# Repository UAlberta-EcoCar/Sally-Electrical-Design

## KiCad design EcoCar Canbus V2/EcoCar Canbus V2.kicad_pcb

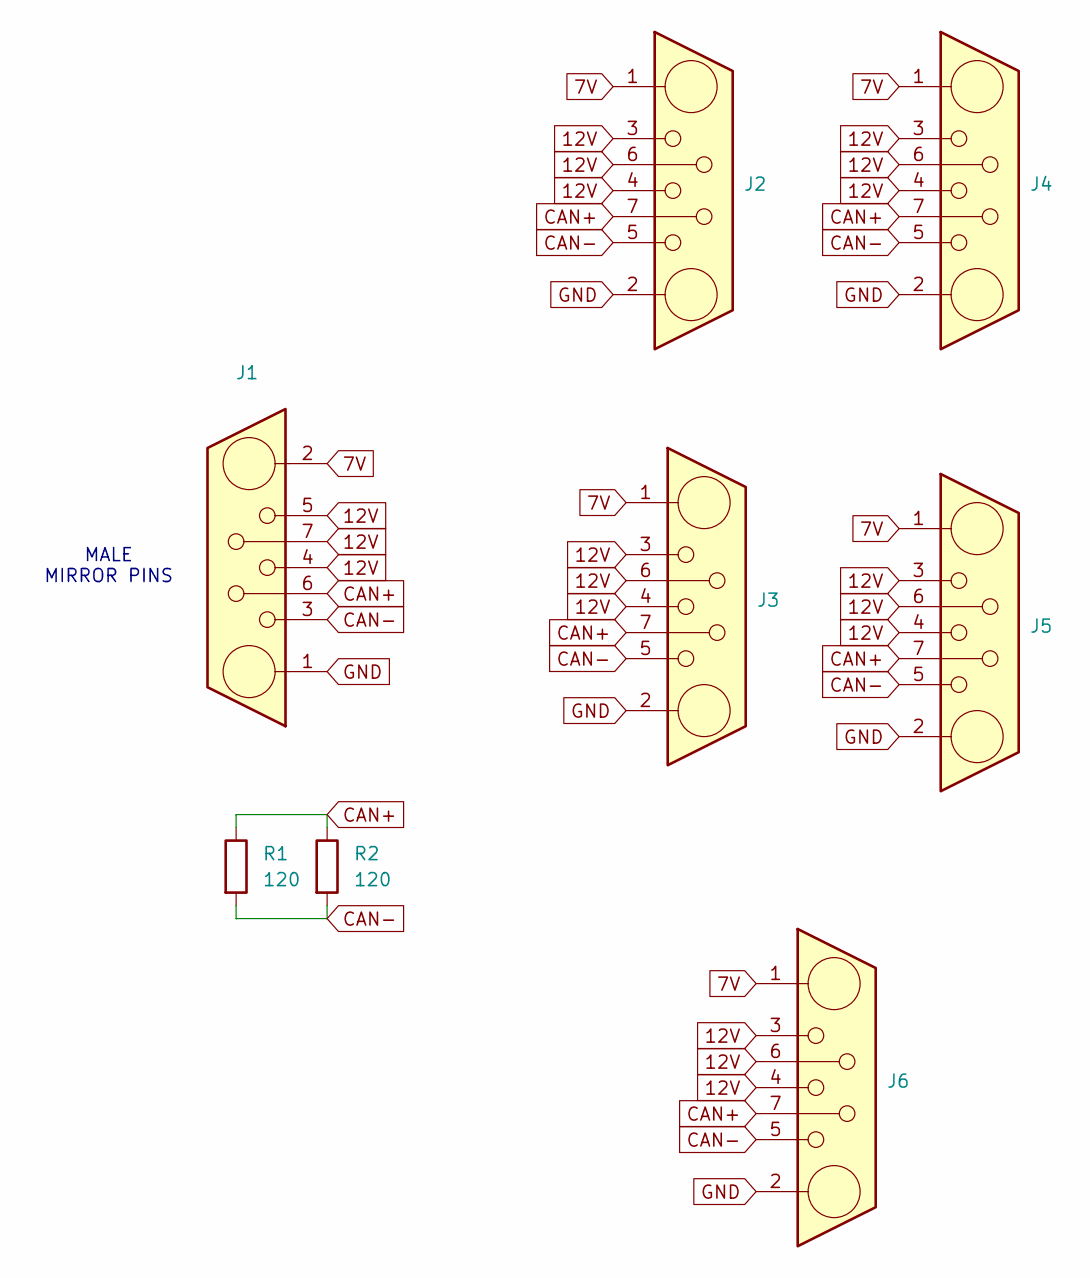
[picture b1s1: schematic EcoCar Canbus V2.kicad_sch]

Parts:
J1, J2, J3, J4, J5, J6: DB7W2-30A
R1, R2: 120; R_Axial_DIN0207_L6.3mm_D2.5mm_P7.62mm_Horizontal

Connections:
7V: J1.2, J2.1, J3.1, J4.1, J5.1, J6.1
12V: J1.4, J1.5, J1.7, J2.3, J2.4, J2.6, J3.3, J3.4, J3.6, J4.3, J4.4, J4.6, J5.3, J5.4, J5.6, J6.3, J6.4, J6.6
CAN+: J1.6, J2.7, J3.7, J4.7, J5.7, J6.7, R1.1, R2.1
CAN-: J1.3, J2.5, J3.5, J4.5, J5.5, J6.5, R1.2, R2.2
GND: J1.1, J2.2, J3.2, J4.2, J5.2, J6.2

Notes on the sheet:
MALE MIRROR PINS

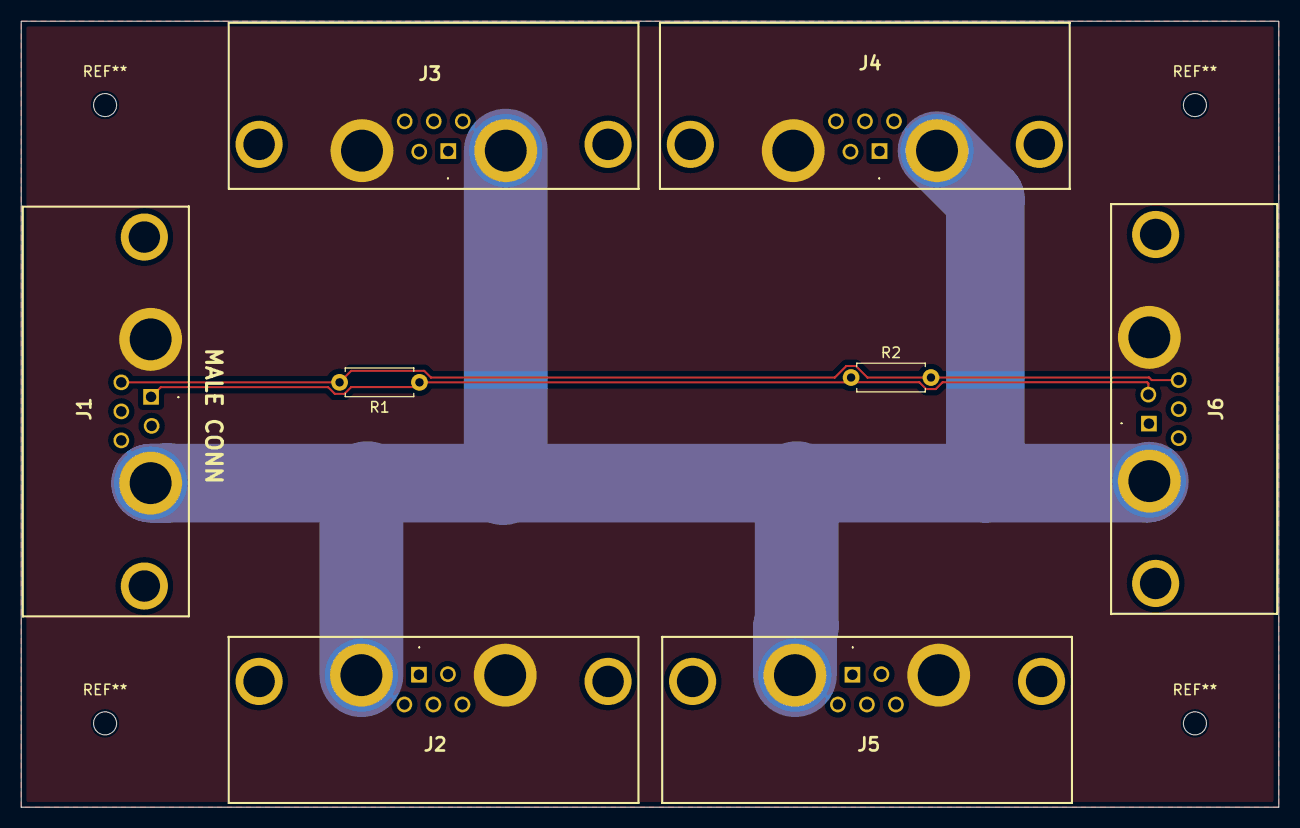
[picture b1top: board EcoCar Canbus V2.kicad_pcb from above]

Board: 4 copper layers, 120.0 x 75.0 mm, 8 parts (0 on the bottom side), 5 nets.

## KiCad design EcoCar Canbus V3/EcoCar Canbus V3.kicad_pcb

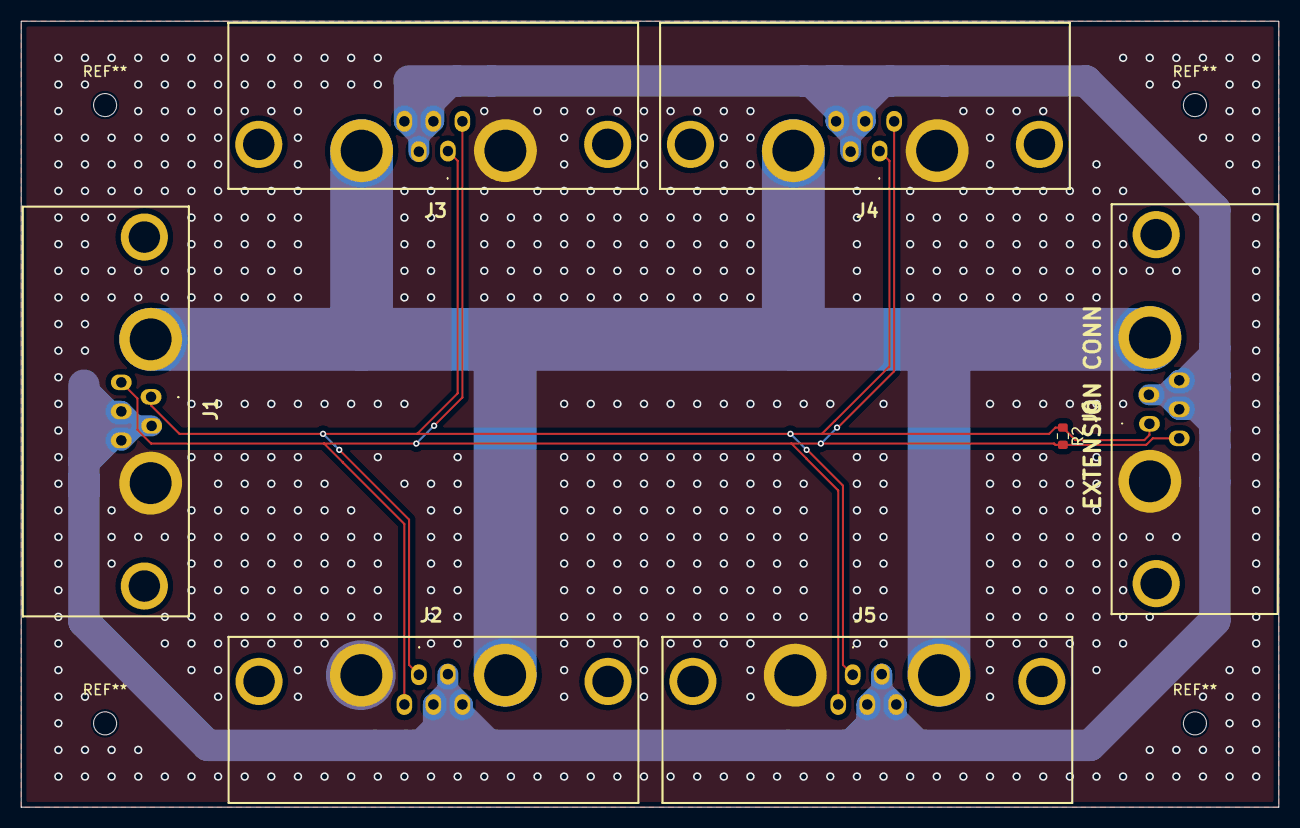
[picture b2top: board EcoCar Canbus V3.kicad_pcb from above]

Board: 4 copper layers, 120.0 x 75.0 mm, 7 parts (0 on the bottom side), 5 nets.

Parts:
J1: DB7W2-Male
J2, J3, J4, J5, J6: DB7W2-Female
R2: 120; R_0603_1608Metric

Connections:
7V: J1.A1, J2.8 (A1), J3.8 (A1), J4.8 (A1), J5.8 (A1), J6.8 (A1)
12V: J1.2, J1.4, J1.5, J2.1, J2.3, J2.4, J3.1, J3.3, J3.4, J4.1, J4.3, J4.4, J5.1, J5.3, J5.4, J6.1, J6.3, J6.4
CAN+: J1.1, J2.2, J3.2, J4.2, J5.2, J6.2, R2.1
CAN-: J1.3, J2.5, J3.5, J4.5, J5.5, J6.5, R2.2
GND: J1.A2, J2.9 (A2), J3.9 (A2), J4.9 (A2), J5.9 (A2), J6.9 (A2)

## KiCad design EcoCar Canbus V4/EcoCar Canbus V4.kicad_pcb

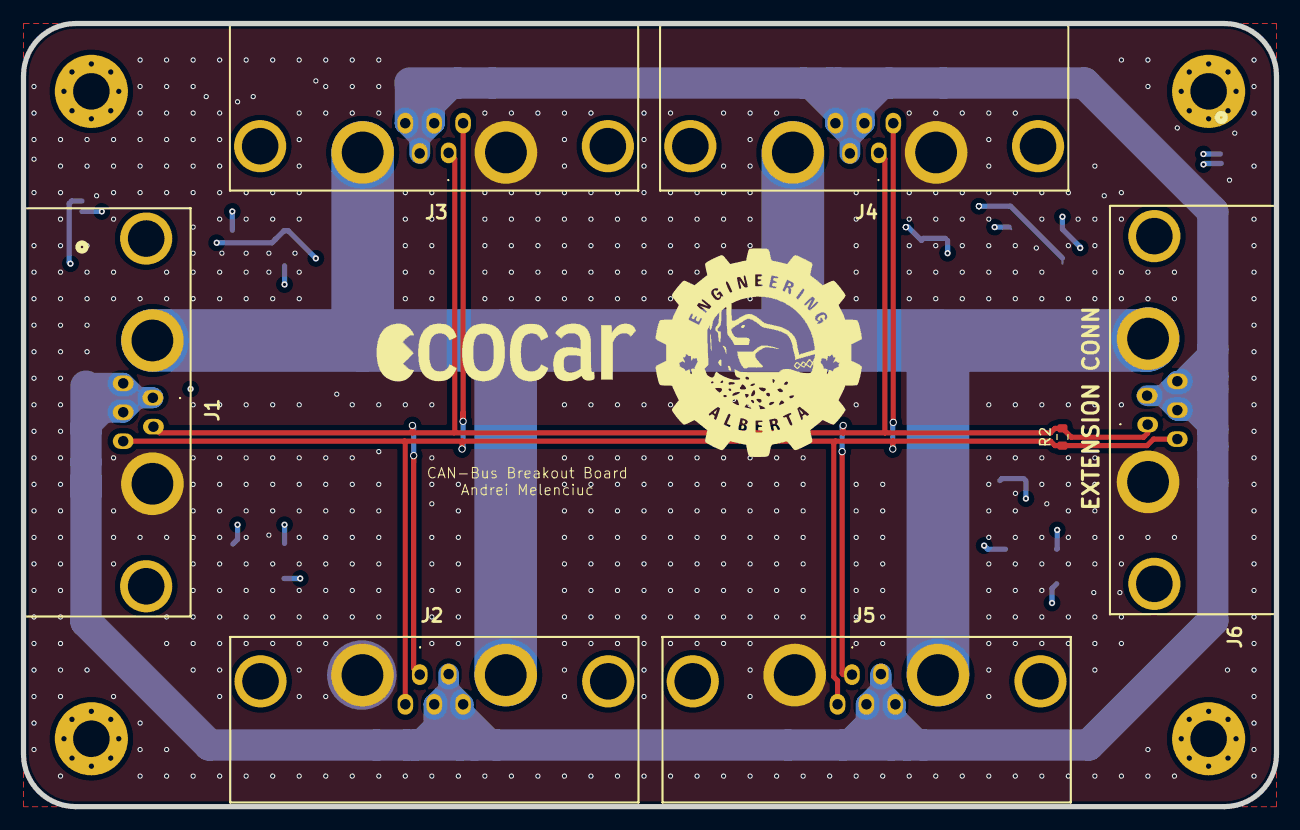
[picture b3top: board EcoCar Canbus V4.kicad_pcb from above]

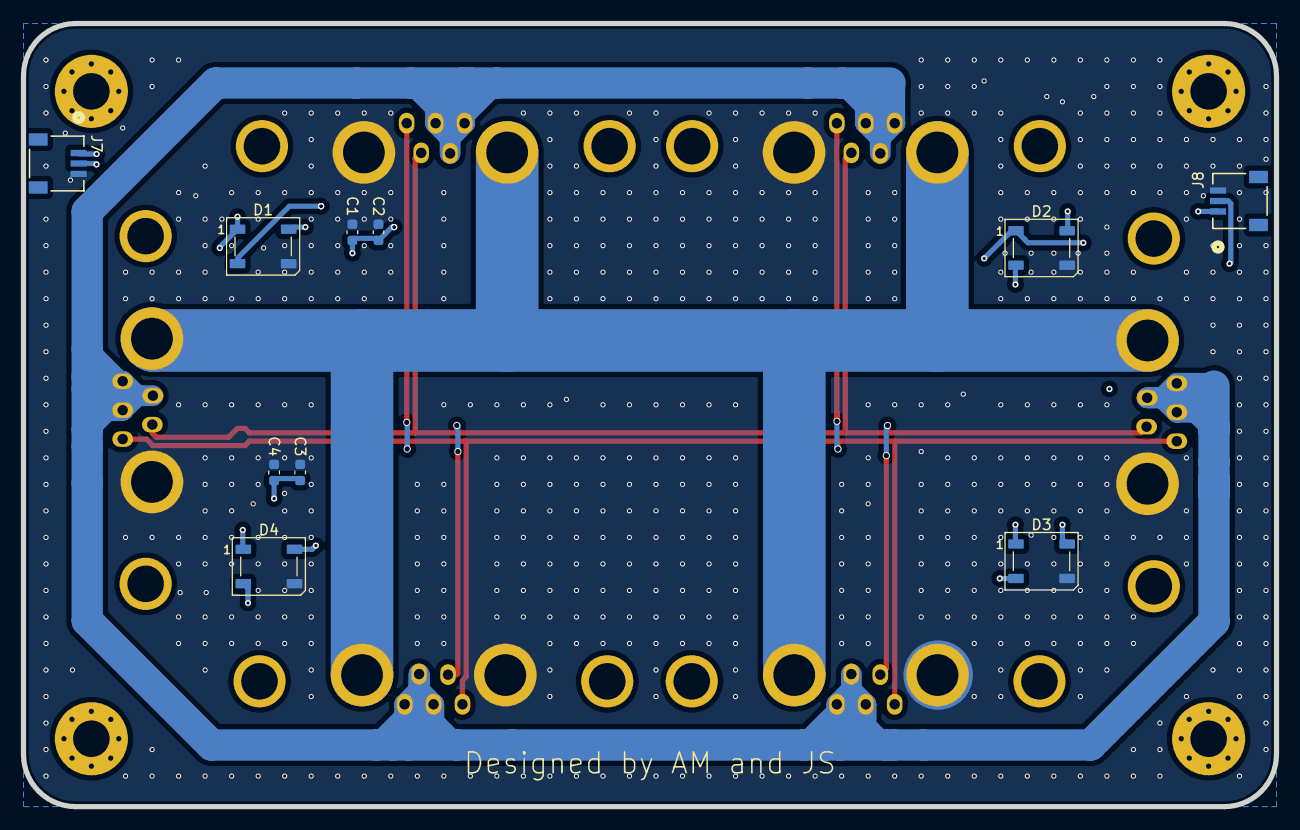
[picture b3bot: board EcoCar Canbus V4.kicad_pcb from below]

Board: 4 copper layers, 120.0 x 75.0 mm, 17 parts (10 on the bottom side), 11 nets.

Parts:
C1, C2, C3, C4: 1n; C_0603_1608Metric
D1, D2, D3, D4: WS2812B; LED_WS2812B_PLCC4_5.0x5.0mm_P3.2mm
J1: DB7W2-Male
J2, J3, J4, J5, J6: DB7W2-Female
J7, J8: Conn_01x03_Pin; CONN_SM03B-SRSS-TB_JST
R2: 120; R_0603_1608Metric

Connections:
7V: J1.8, J2.8, J3.8, J4.8, J5.8, J6.8
12V: J1.1, J1.3, J1.4, J2.1, J2.3, J2.4, J3.1, J3.3, J3.4, J4.1, J4.3, J4.4, J5.1, J5.3, J5.4, J6.1, J6.3, J6.4
+5V: C1.1, C2.1, C3.1, C4.1, D1.1 (VDD), D2.1 (VDD), D3.1 (VDD), D4.1 (VDD), J7.1, J8.1
/DIN: D1.4 (DIN), J7.2
/DOUT: D4.2 (DOUT), J8.2
CAN+: J1.2, J2.2, J3.2, J4.2, J5.2, J6.2, R2.1
CAN-: J1.5, J2.5, J3.5, J4.5, J5.5, J6.5, R2.2
GND: C1.2, C2.2, C3.2, C4.2, D1.3 (VSS), D2.3 (VSS), D3.3 (VSS), D4.3 (VSS), J1.9, J2.9, J3.9, J4.9, J5.9, J6.9, J7.3, J8.3
unnamed: D1.2 (DOUT), D2.4 (DIN)
unnamed: D2.2 (DOUT), D3.4 (DIN)
unnamed: D3.2 (DOUT), D4.4 (DIN)

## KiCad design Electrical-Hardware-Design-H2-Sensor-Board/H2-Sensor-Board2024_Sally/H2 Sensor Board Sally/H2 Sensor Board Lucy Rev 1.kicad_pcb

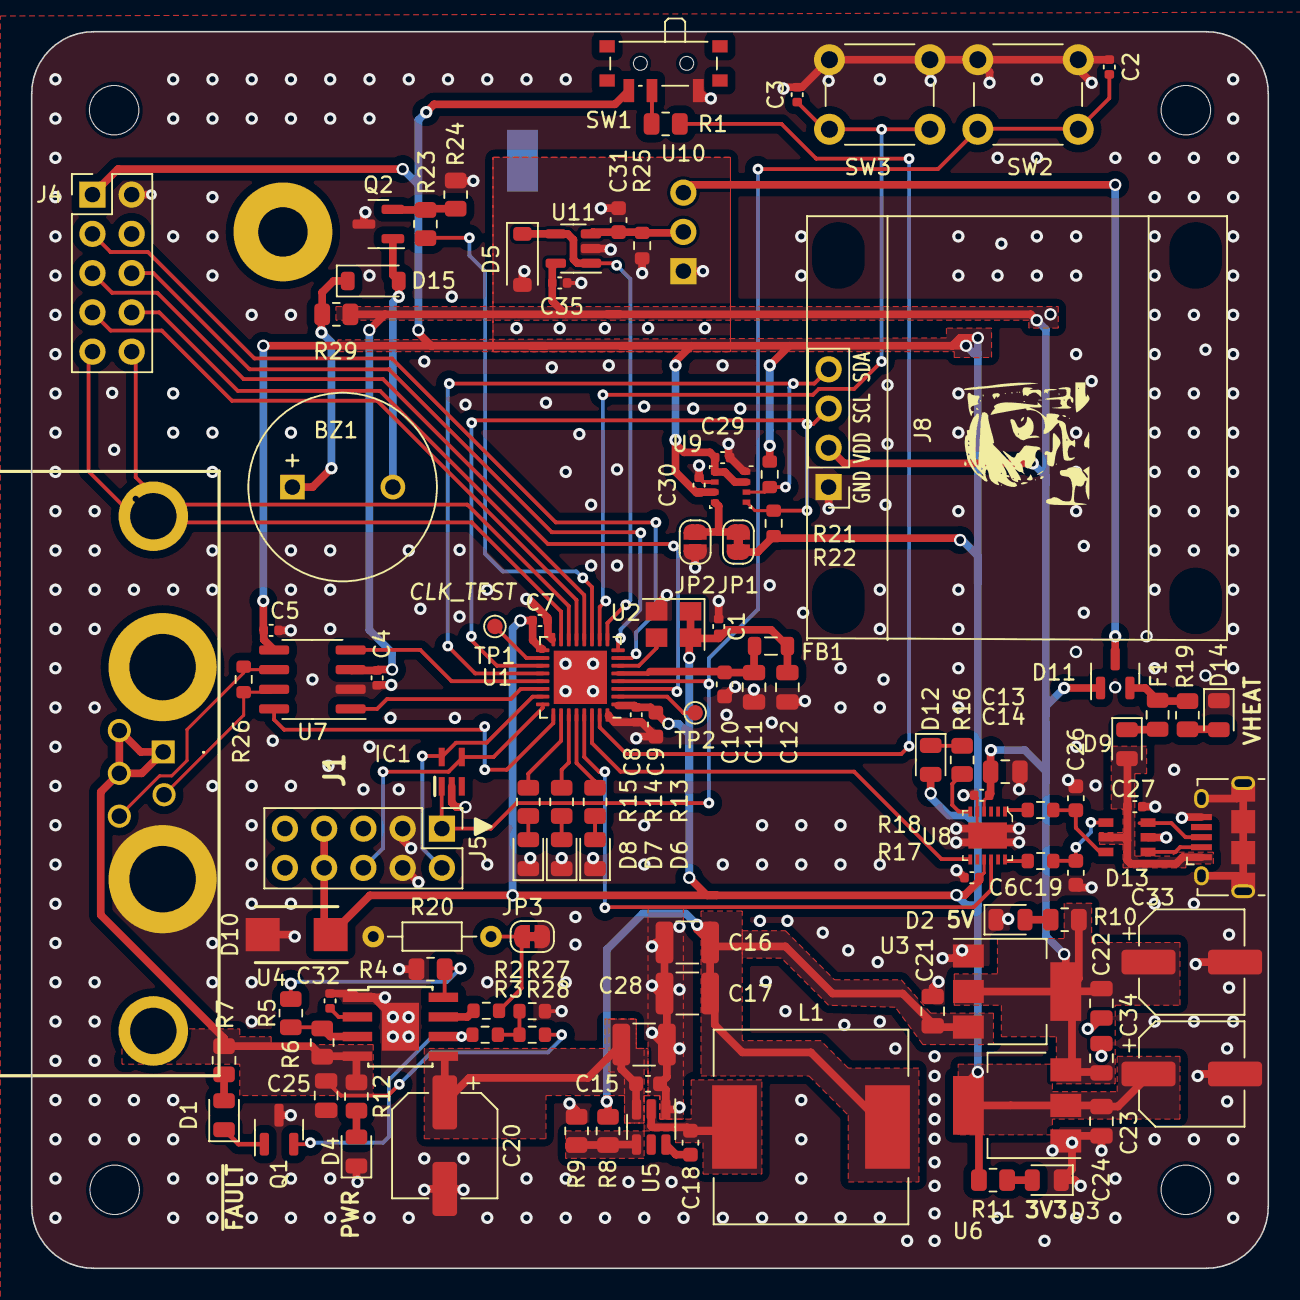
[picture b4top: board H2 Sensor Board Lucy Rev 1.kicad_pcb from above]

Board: 2 copper layers, 80.0 x 80.0 mm, 115 parts (1 on the bottom side), 74 nets.

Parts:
BZ1: Buzzer; MagneticBuzzer_ProSignal_ABT-410-RC
C1, C2, C3, C4, C5, C6, C7, C8, C14, C27, C29, C30, C35: 100n; C_0402_1005Metric
C9, C10: 10u; C_0603_1608Metric
C11, C12: 1u; C_0805_2012Metric
C13: 4u7; C_0805_2012Metric
C15, C18, C31: 100n; C_0603_1608Metric
C16, C17: 22u; C_1210_3225Metric
C19, C26: 47p; C_0603_1608Metric
C20: 100u; CP_Elec_6.3x5.9
C21, C23: 10u; C_0805_2012Metric
C22, C24: 22u; C_0805_2012Metric
C25: 100n; C_0805_2012Metric
C28: 10u; C_1210_3225Metric
C32: 2n2; C_0402_1005Metric
C33, C34: 22u; CP_Elec_6.3x5.9
D1, D6: GREEN; LED_0805_2012Metric
D2, D3, D4, D14: BLUE; LED_0805_2012Metric
D5: MMSZ5226B-7-F; D_SOD-123
D7: RED; LED_0805_2012Metric
D8, D12: AMBER; LED_0805_2012Metric
D9: D_Schottky; D_0805_2012Metric
D10: SMLVT3V3; DIOM5436X265N
D11: BAT54C; SOT-23
D13: USBLC6-2SC6; SOT23-6L_STM
D15: BAV16W/1N4148W; D_SOD-123
F1: 500mA; Fuse_0805_2012Metric
FB1: 300R; L_0805_2012Metric
H1, H2, H3, H4: MountingHole; MountingHole_3.2mm_M3
IC1: ESDALC6V1W5; SOT65P210X110-5N
J1: DB7W2-30A
J4: GPIO; PinHeader_2x05_P2.54mm_Vertical
J5: Conn_02x05_Top_Bottom; PinHeader_2x05_P2.54mm_Vertical
J6: USB_B_Micro; USB_Micro-B_Amphenol_10118194_Horizontal
J8: OLED; Display_128x64_096_I2C
JP1: Slave Address LSB 1; SolderJumper-2_P1.3mm_Bridged_RoundedPad1.0x1.5mm
JP2: Slave Address LSB 0; SolderJumper-2_P1.3mm_Open_RoundedPad1.0x1.5mm
JP3: MAX CURRENT; SolderJumper-2_P1.3mm_Bridged_RoundedPad1.0x1.5mm
L1: 3u8; L_12x12mm_H8mm
NT1: NetTie_2; NetTie-2_SMD_Pad2.0mm
Q1: NMOS; SOT-23
Q2: NMOS IRLML2502TRPBF; SOT-23
R1, R24: 10k; R_0805_2012Metric
R2: 620R; R_0603_1608Metric
R3, R21, R22, R25: 4k7; R_0603_1608Metric
R4, R8: 47k; R_0805_2012Metric
R5: 23k7; R_0805_2012Metric
R6: 511k; R_0805_2012Metric
R7, R12: 2k; R_0805_2012Metric
R9: 6k2; R_0805_2012Metric
R10, R19: 560R; R_0805_2012Metric
R11, R13, R14, R15, R16: 220R; R_0805_2012Metric
R17, R18: 27R; R_0603_1608Metric
R20: R; R_Axial_DIN0204_L3.6mm_D1.6mm_P7.62mm_Horizontal
R23: 10R; R_0805_2012Metric
R26: 120R; R_0603_1608Metric
R27: 30k; R_0603_1608Metric
R28: 47k; R_0603_1608Metric
R29: 1k; R_0805_2012Metric
SW1: SW_SPDT; SW_SPDT_PCM12
SW2: RESET; SW_PUSH_6mm_H5mm
SW3: TARE; SW_PUSH_6mm_H5mm
TP1: MCO; TestPoint_Pad_D1.0mm
TP2: GPTP; TestPoint_Pad_D1.0mm
U1: STM32L432KCU6; QFN-32-1EP_5x5mm_P0.5mm_EP3.45x3.45mm
U2: 8MHz; Crystal_SMD_3225-4Pin_3.2x2.5mm
U3: AZ1117IH-5.0; SOT-223-3_TabPin2
U4: TPS2596; TI_SO-PowerPAD-8
U5: AP62250; TSOT-23-6
U6: AZ1117IH-3.3; SOT-223-3_TabPin2
U7: MCP2542FD-E/SN; SOIC-8_3.9x4.9mm_P1.27mm
U8: FT234XD-R; DFN-12-1EP_3x3mm
U9: BME280; Bosch_LGA-8_2.5x2.5mm_P0.65mm_ClockwisePinNumbering
U10: H2_Sensor_Daughter_Board_Rev_1
U11: AD8603; TSOT-23-5

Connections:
+3.3VA: C10.1, C11.1, FB1.1, U1.5 (VDDA)
+3V3: C1.2, C5.2, C6.1, C7.1, C8.1, C9.1, C12.1, C24.1, C29.1, C30.1, C34.1, D10.1 (K), D12.2 (A), FB1.2, J4.1, J5.7, J5.8, JP1.2 (B), R11.1, R21.1, R22.1, SW1.3 (C), U1.1 (VDD), U1.17 (VDD), U2.1 (~ST), U2.4 (VCC), U6.2 (VO), U7.5 (VIO), U8.9 (VCCIO), U9.2 (CSB), U9.6 (VDDIO), U9.8 (VDD)
+5V: C4.2, C13.1, C14.1, C22.1, C23.1, C33.1, C35.1, D11.1, J8.2, R10.1, R29.1, U3.2 (VO), U6.3 (VI), U7.3 (VDD), U8.4 (VCC), U11.5 (V+)
+12V: C15.1, C20.1, C28.1, U4.5 (OUT), U5.3 (VIN)
/12volts_sys: C25.1, J1.3, J1.4, J1.6, R6.2, R7.1, R12.1, R28.1, U4.4 (IN)
/BEEPER: R23.2, U1.11 (PA5)
/BOOT0: R1.2, U1.31 (PH3)
/CAN_RX: U1.21 (PA11), U7.4 (RXD)
/CAN_STBY: U1.25 (PA15), U7.8 (STBY)
/CAN_TX: U1.22 (PA12), U7.1 (TXD)
/CD+: J1.7, R26.1, U7.7 (CANH)
/CD-: J1.5, R26.2, U7.6 (CANL)
/DEBUG_SWCLK: IC1.4 (I/03), J5.6, U1.24 (PA14)
/DEBUG_SWDIO: IC1.5 (I/04), J5.2, U1.23 (PA13)
/GPIO1: J4.8, U1.12 (PA6)
/GPIO2: J4.10, U1.14 (PB0)
/GPIO3: J4.5, U1.3 (PC15)
/GPIO4: J4.6, U1.8 (PA2)
/GPIO7: J4.9, U1.15 (PB1)
/GPIO8: J4.7, U1.13 (PA7)
/GPIO9: J4.3, U1.7 (PA1)
/GPLED1: R15.2, U1.26 (PB3)
/GPLED2: R14.2, U1.27 (PB4)
/GPLED3: R13.2, U1.28 (PB5)
/H2_SENSE: D5.1 (K), U1.9 (PA3), U11.1, U11.4 (-)
/NRST: C2.2, IC1.1 (I/01), J5.1, SW2.2, U1.4 (NRST)
/Power/7V: C16.1, C17.1, C21.1, L1.2, R8.1, U3.3 (VI)
/Power/FB: R8.2, R9.2, U5.4 (FB)
/Power/I_{MON}: R2.1, U4.7 (ILM)
/Power/SW: C18.1, L1.1, U5.2 (SW)
/Power/~FAULT: Q1.2 (G), R3.1, U4.6 (~FAULT)
/SCL: J8.3, R22.2, U1.19 (PA9), U9.4 (SCK)
/SDA: J8.4, R21.2, U1.20 (PA10), U9.3 (SDI)
/Sensors/ADDR: JP1.1 (A), JP2.1 (A), U9.5 (SDO)
/Sensors/V_SENSE: C31.1, R25.2, U10.2 (V_SENSE), U11.3 (+)
/TARE: C3.2, SW3.2, U1.10 (PA4)
/UART_RX: U1.30 (PB7), U8.7 (TXD)
/UART_TX: U1.29 (PB6), U8.10 (RXD)
/XCLK: U1.6 (PA0), U2.3 (OUT)
GND: C1.1, C2.1, C3.1, C4.1, C5.1, C6.2, C7.2, C8.2, C9.2, C10.2, C11.2, C12.2, C13.2, C14.2, C15.2, C16.2, C17.2, C19.1, C20.2, C21.2, C22.2, C23.2, C24.2, C25.2, C26.1, C27.1, C28.2, C29.2, C30.2, C32.2, C33.2, C34.2, D2.1 (K), D3.1 (K), D4.1 (K), D6.1 (K), D7.1 (K), D8.1 (K), D10.2 (A), D13.2, D14.1 (K), IC1.2 (GND), J1.2, J4.2, J5.3, J5.4, J6.5 (GND), J6.6 (Shield), J8.1, JP2.2 (B), JP3.2 (B), NT1.2, Q1.3 (S), Q2.3 (S), R4.2, R9.1, R20.1, R24.2, R27.1, SW1.1 (A), SW2.1, SW3.1, U1.16 (VSS), U1.32 (VSS), U1.33 (VSS), U2.2 (GND), U3.1 (GND), U4.1 (GND), U4.9 (PAD), U5.1 (GND), U6.1 (GND), U7.2 (VSS), U8.5 (GND), U8.13 (GND), U9.1 (GND), U9.7 (GND)
GNDA: C31.2, C35.2, D5.2 (A), NT1.1, R25.1, U10.1 (GND), U11.2 (V-)
unnamed: BZ1.2 (+), D15.2 (A), Q2.1 (D)
unnamed: BZ1.1 (-), D15.1 (K), R29.2
unnamed: C19.2, D13.4, R17.2
unnamed: C26.2, D13.6, R18.2
unnamed: D1.2 (A), R7.2
unnamed: D1.1 (K), Q1.1 (D)
unnamed: D2.2 (A), R10.2
unnamed: D3.2 (A), R11.2
unnamed: D4.2 (A), R12.2
unnamed: D6.2 (A), R13.1
unnamed: D7.2 (A), R14.1
unnamed: D8.2 (A), R15.1
unnamed: D9.1 (K), F1.1
unnamed: D12.1 (K), R16.2
unnamed: D14.2 (A), R19.2
unnamed: D13.3, J6.3 (D+)
unnamed: D13.1, J6.2 (D-)
unnamed: JP3.1 (A), R2.2, R20.2
unnamed: Q2.2 (G), R23.1, R24.1
unnamed: R3.2, R27.2, R28.2
unnamed: R1.1, SW1.2 (B)
unnamed: TP1.1, U1.18 (PA8)
unnamed: TP2.1, U1.2 (PC14)
unnamed: R5.1, R6.1, U4.3 (EN/UVLO)
unnamed: R4.1, R5.2, U4.8 (OVLO)
unnamed: C32.1, U4.2 (dV/dT)
unnamed: C18.2, U5.6 (BST)
unnamed: R16.1, U8.6 (CBUS0)
unnamed: R18.1, U8.1 (USBDM)
unnamed: R17.1, U8.12 (USBDP)
unnamed: D11.3, U10.3 (V_HEAT)
VBUS_UP: C27.2, D9.2 (A), D13.5, J6.1 (VBUS)
V_HEAT: D11.2, F1.2, R19.1

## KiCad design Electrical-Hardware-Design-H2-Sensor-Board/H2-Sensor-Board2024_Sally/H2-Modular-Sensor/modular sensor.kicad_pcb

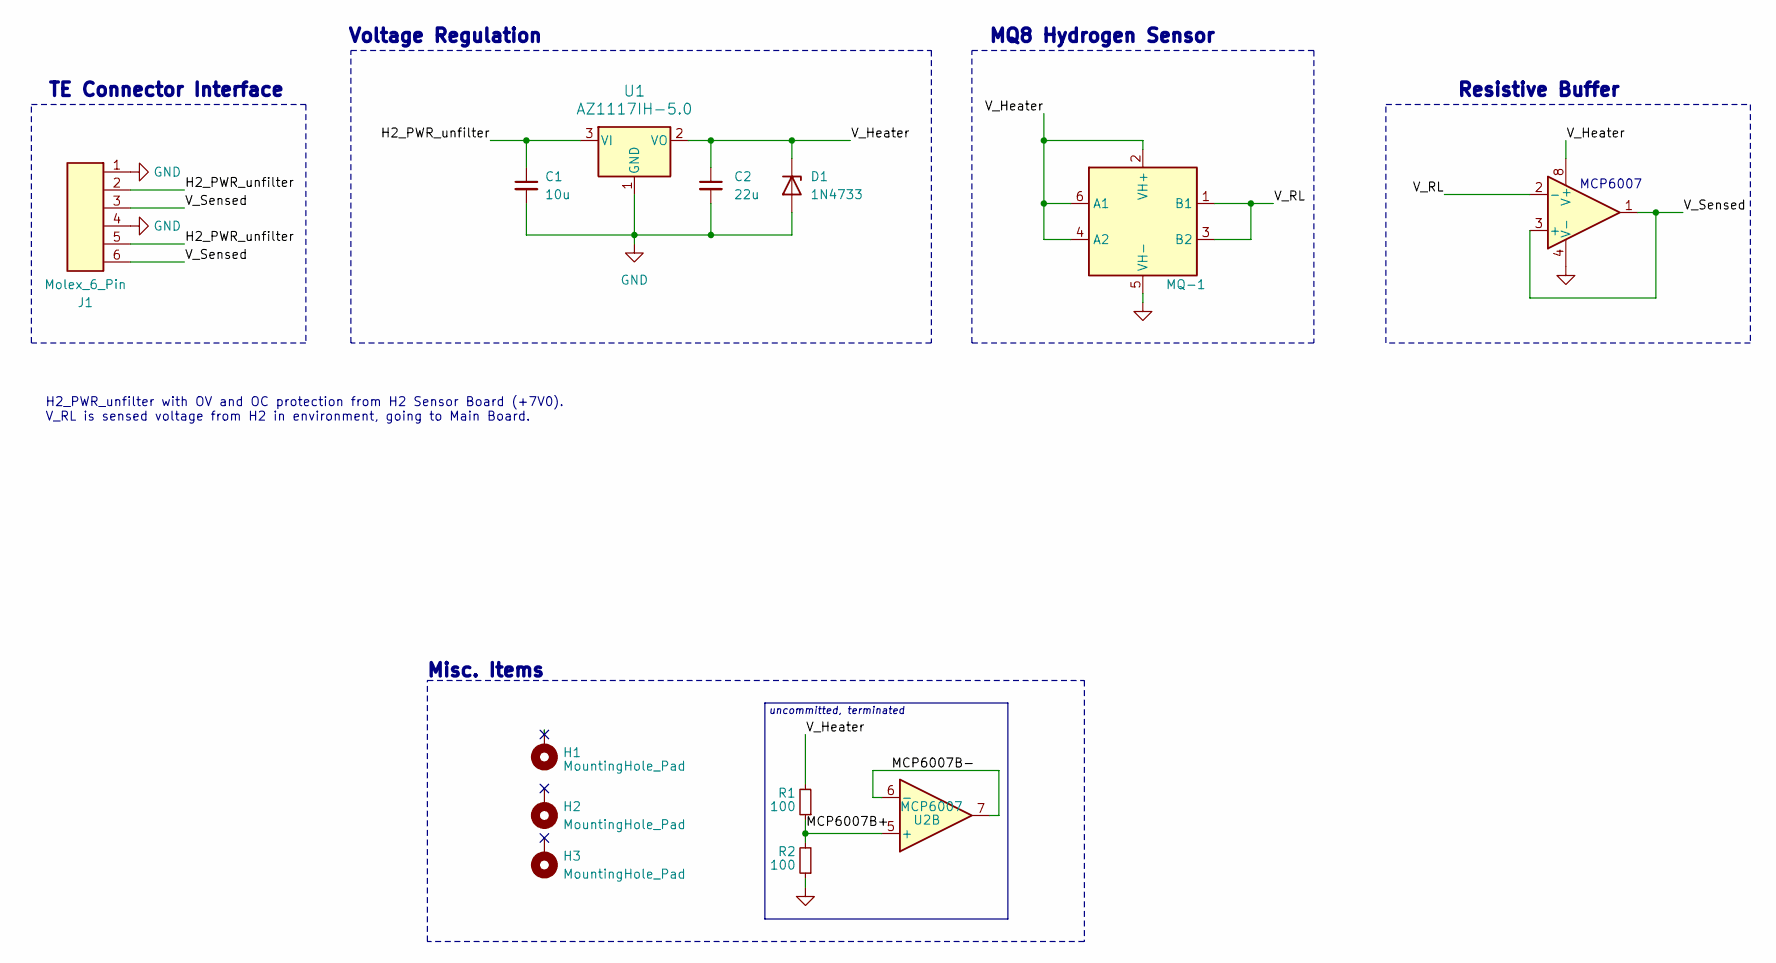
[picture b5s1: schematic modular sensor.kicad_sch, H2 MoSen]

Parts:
C1: 10u; C_0603_1608Metric
C2: 22u; C_0603_1608Metric
D1: 1N4733; D_DO-41_SOD81_P10.16mm_Horizontal; lcsc C5122130
H1, H2, H3: MountingHole_Pad; MountingHole_3.2mm_M3_Pad
J1: Molex_6_Pin; Molex_6_pin_RightAngle
MQ-1: MQ-8
R1, R2: 100; R_0603_1608Metric
U1: AZ1117IH-5.0; SOT-223-3_TabPin2
U2: MCP6007; SOIC-8_3.9x4.9mm_P1.27mm

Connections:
/H2_PWR_unfilter: C1.1, J1.2, J1.5, U1.3 (VI)
/MCP6007B+: R1.1, R2.2, U2.5 (+)
/MCP6007B-: U2.6 (-), U2.7
/V_Heater: C2.1, D1.1 (K), MQ-1.2 (VH+), MQ-1.4 (A2), MQ-1.6 (A1), R1.2, U1.2 (VO), U2.8 (V+)
/V_RL: MQ-1.1 (B1), MQ-1.3 (B2), U2.2 (-)
/V_Sensed: J1.3, J1.6, U2.1, U2.3 (+)
GND: C1.2, C2.2, D1.2 (A), J1.1, J1.4, MQ-1.5 (VH-), R2.1, U1.1 (GND), U2.4 (V-)

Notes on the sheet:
TE Connector Interface
Voltage Regulation
Resistive Buffer
MQ8 Hydrogen Sensor
H2_PWR_unfilter with OV and OC protection from H2 Sensor Board (+7V0). V_RL is sensed voltage from H2 in environment, going to Main Board.
MCP6007
uncommitted, terminated
Misc. Items

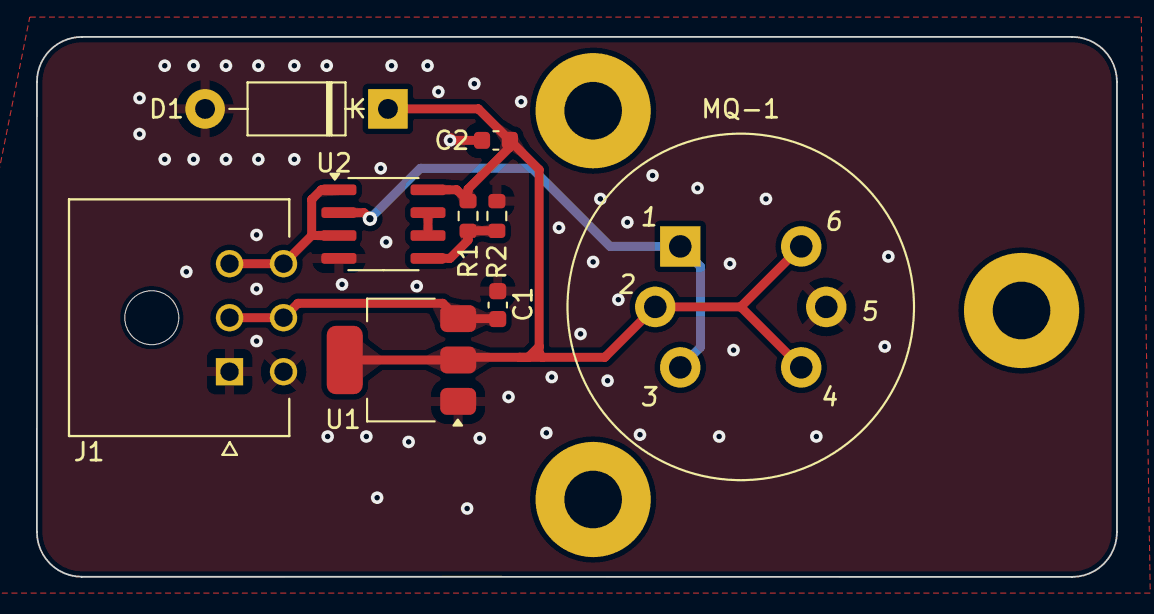
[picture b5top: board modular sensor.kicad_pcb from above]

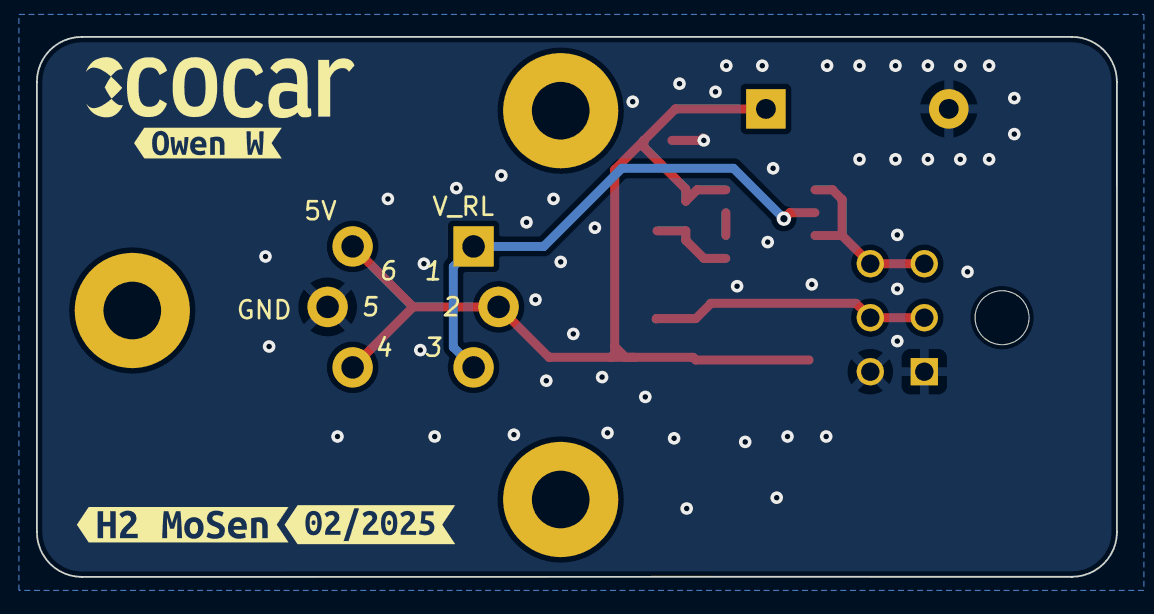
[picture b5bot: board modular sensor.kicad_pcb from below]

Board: 2 copper layers, 60.0 x 30.0 mm, 15 parts (3 on the bottom side), 7 nets.

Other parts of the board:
kibuzzard-67B982E7: G***; kibuzzard-67B982E7
kibuzzard-67B98323: G***; kibuzzard-67B98323
kibuzzard-67B98359: G***; kibuzzard-67B98359

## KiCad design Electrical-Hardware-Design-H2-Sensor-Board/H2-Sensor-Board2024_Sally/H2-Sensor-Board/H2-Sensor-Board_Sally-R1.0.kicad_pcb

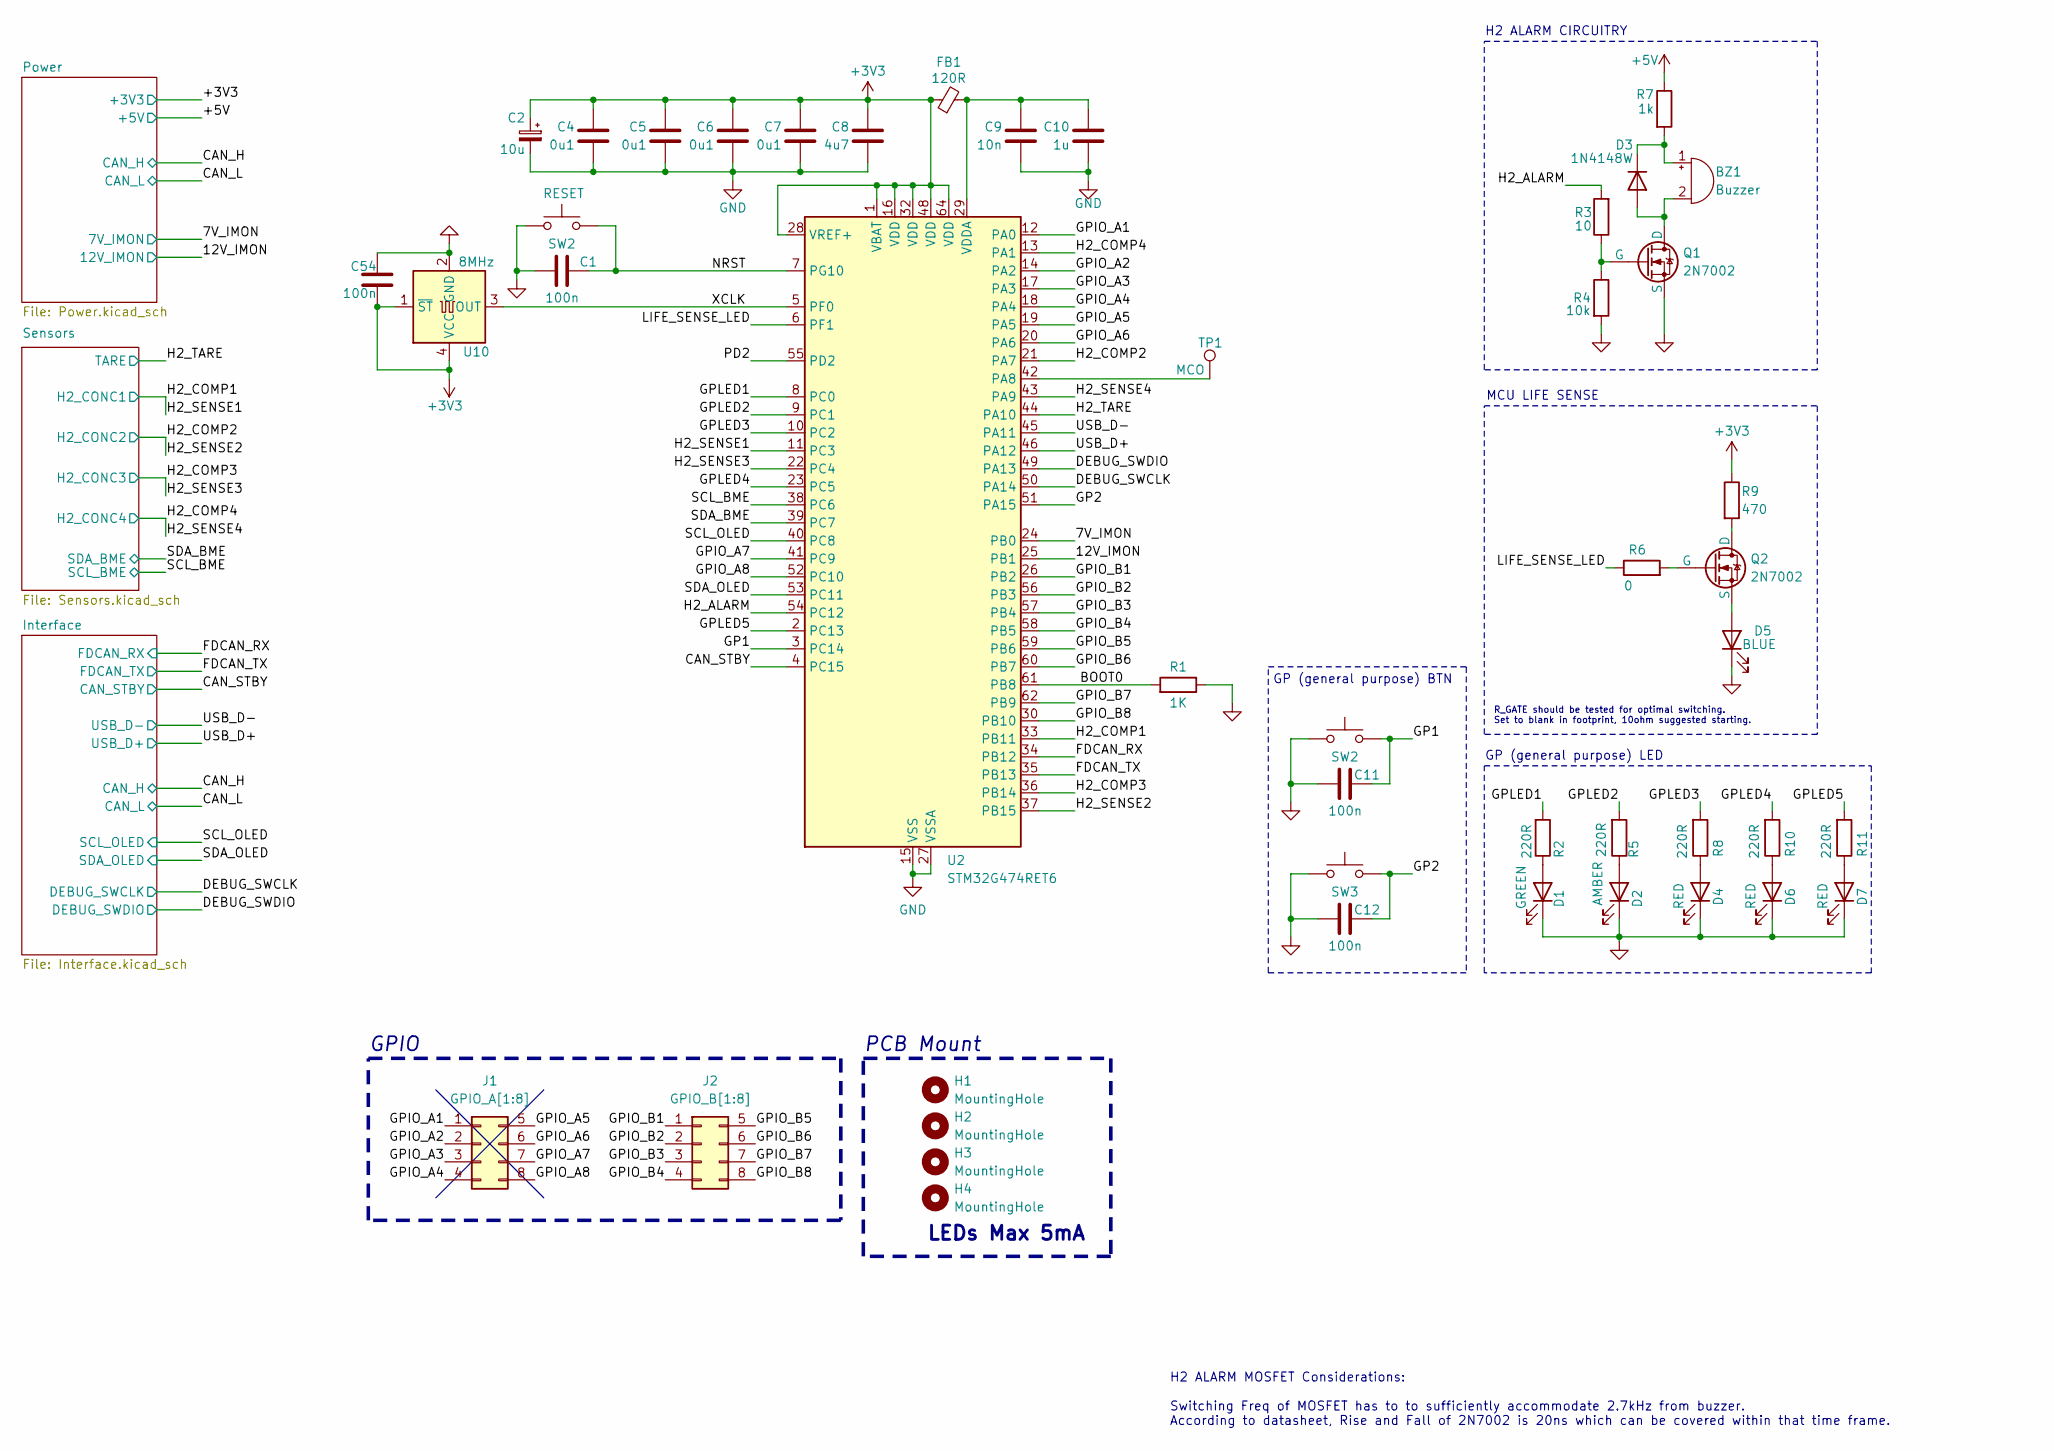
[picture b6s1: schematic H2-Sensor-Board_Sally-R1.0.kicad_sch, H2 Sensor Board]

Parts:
BZ1: Buzzer; MagneticBuzzer_ProSignal_ABT-410-RC; JLCPCB Part#(optional) C96256
C1, C11, C12, C54: 100n; C_0603_1608Metric; JLCPCB Part#(Optional) C1525
C2: 10u; C_1210_3225Metric; lcsc C43345
C4, C5, C6, C7: 0u1; C_0603_1608Metric
C8: 4u7; C_0603_1608Metric
C9: 10n; C_0603_1608Metric
C10: 1u; C_0603_1608Metric
D1: GREEN; LED_0603_1608Metric_Pad1.05x0.95mm_HandSolder; JLCPCB Part#(Optional) C2297
D2: AMBER; LED_0603_1608Metric_Pad1.05x0.95mm_HandSolder; JLCPCB Part#(Optional) C84256
D3: 1N4148W; D_SOD-123
D4, D6, D7: RED; LED_0603_1608Metric_Pad1.05x0.95mm_HandSolder; JLCPCB Part#(Optional) C2296
D5: BLUE; LED_0603_1608Metric_Pad1.05x0.95mm_HandSolder
FB1: 120R; L_0603_1608Metric
H1: MountingHole; MountingHole_3.2mm_M3
H2, H3, H4: MountingHole; MountingHole_3.5mm
J1: GPIO_A[1:8]; PinHeader_2x04_P2.54mm_Vertical
J2: GPIO_B[1:8]; PinHeader_2x04_P2.54mm_Vertical
Q1, Q2: 2N7002; SOT-23
R1: 1K; R_0603_1608Metric; JLCPCB Part#(Optional) C17414
R2, R5, R8, R10, R11: 220R; R_0603_1608Metric; JLCPCB Part#(Optional) C17557
R3: 10; R_0603_1608Metric; JLCPCB Part#(Optional) C17415
R4: 10k; R_0603_1608Metric; JLCPCB Part#(Optional) C17414
R6: 0; R_0603_1608Metric; JLCPCB Part#(Optional) C17415
R7: 1k; R_0603_1608Metric; JLCPCB Part#(Optional) C17513
R9: 470; R_0603_1608Metric; JLCPCB Part#(Optional) C17513
SW2, SW3: TARE BUTTON; SW_PUSH_6mm_H5mm
TP1: MCO; TestPoint_Pad_D1.0mm
U2: STM32G474RET6; LQFP-64_10x10mm_P0.5mm
U10: 8MHz; Crystal_SMD_3225-4Pin_3.2x2.5mm

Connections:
+5V: R7.1; also elsewhere on the board
/7V_IMON: U2.24 (PB0); also elsewhere on the board
/12V_IMON: U2.25 (PB1); also elsewhere on the board
/BOOT0: R1.2, U2.61 (PB8)
/CAN_STBY: U2.4 (PC15); also elsewhere on the board
/DEBUG_SWCLK: U2.50 (PA14); also elsewhere on the board
/DEBUG_SWDIO: U2.49 (PA13); also elsewhere on the board
/FDCAN_RX: U2.34 (PB12); also elsewhere on the board
/FDCAN_TX: U2.35 (PB13); also elsewhere on the board
/GP2: C12.2, SW3.2, U2.51 (PA15)
/GPIO_A1: J1.1, U2.12 (PA0)
/GPIO_A2: J1.2, U2.14 (PA2)
/GPIO_A3: J1.3, U2.17 (PA3)
/GPIO_A4: J1.4, U2.18 (PA4)
/GPIO_A5: J1.5, U2.19 (PA5)
/GPIO_A6: J1.6, U2.20 (PA6)
/GPIO_A7: J1.7, U2.41 (PC9)
/GPIO_A8: J1.8, U2.52 (PC10)
/GPIO_B1: J2.1, U2.26 (PB2)
/GPIO_B2: J2.2, U2.56 (PB3)
/GPIO_B3: J2.3, U2.57 (PB4)
/GPIO_B4: J2.4, U2.58 (PB5)
/GPIO_B5: J2.5, U2.59 (PB6)
/GPIO_B6: J2.6, U2.60 (PB7)
/GPIO_B7: J2.7, U2.62 (PB9)
/GPIO_B8: J2.8, U2.30 (PB10)
/GPLED1: R2.2, U2.8 (PC0)
/GPLED2: R5.2, U2.9 (PC1)
/GPLED3: R8.2, U2.10 (PC2)
/GPLED4: R10.2, U2.23 (PC5)
/GPLED5: R11.2, U2.2 (PC13)
/H2_ALARM: R3.2, U2.54 (PC12)
/H2_COMP1: U2.11 (PC3), U2.33 (PB11); also elsewhere on the board
/H2_COMP2: U2.21 (PA7), U2.37 (PB15); also elsewhere on the board
/H2_COMP3: U2.22 (PC4), U2.36 (PB14); also elsewhere on the board
/H2_COMP4: U2.13 (PA1), U2.43 (PA9); also elsewhere on the board
/H2_TARE: U2.44 (PA10); also elsewhere on the board
/LIFE_SENSE_LED: R6.1, U2.6 (PF1)
/PD2: U2.55 (PD2)
/SCL_BME: U2.38 (PC6); also elsewhere on the board
/SCL_OLED: U2.40 (PC8); also elsewhere on the board
/SDA_BME: U2.39 (PC7); also elsewhere on the board
/SDA_OLED: U2.53 (PC11); also elsewhere on the board
/USB_D-: U2.45 (PA11); also elsewhere on the board
GND: C1.1, C2.2, C4.2, C5.2, C6.2, C7.2, C8.2, C9.2, C10.2, C11.1, C12.1, D1.1 (K), D2.1 (K), D4.1 (K), D5.1 (K), D6.1 (K), D7.1 (K), Q1.3 (S), R1.1, R4.2, SW2.1, SW3.1, U2.15 (VSS), U2.27 (VSSA), U2.31 (VSS), U2.47 (VSS), U2.63 (VSS), U10.2 (GND); also elsewhere on the board
unnamed: BZ1.1 (+), D3.1 (K), R7.2
unnamed: BZ1.2 (-), D3.2 (A), Q1.1 (D)
unnamed: D1.2 (A), R2.1
unnamed: D2.2 (A), R5.1
unnamed: D4.2 (A), R8.1
unnamed: D5.2 (A), Q2.3 (S)
unnamed: D6.2 (A), R10.1
unnamed: D7.2 (A), R11.1
unnamed: Q1.2 (G), R3.1, R4.1
unnamed: Q2.1 (D), R9.2
unnamed: Q2.2 (G), R6.2
unnamed: TP1.1, U2.42 (PA8)
unnamed: C9.1, C10.1, FB1.2, U2.29 (VDDA)

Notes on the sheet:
LEDs Max 5mA
R_GATE should be tested for optimal switching. Set to blank in footprint, 10ohm suggested starting.
MCU LIFE SENSE
PCB Mount
GP (general purpose) LED
GP (general purpose) BTN
H2 ALARM CIRCUITRY
H2 ALARM MOSFET Considerations: Switching Freq of MOSFET has to to sufficiently accommodate 2.7kHz from buzzer. According to datasheet, Rise and Fall of 2N7002 is 20ns which can be covered within that time frame.
GPIO
